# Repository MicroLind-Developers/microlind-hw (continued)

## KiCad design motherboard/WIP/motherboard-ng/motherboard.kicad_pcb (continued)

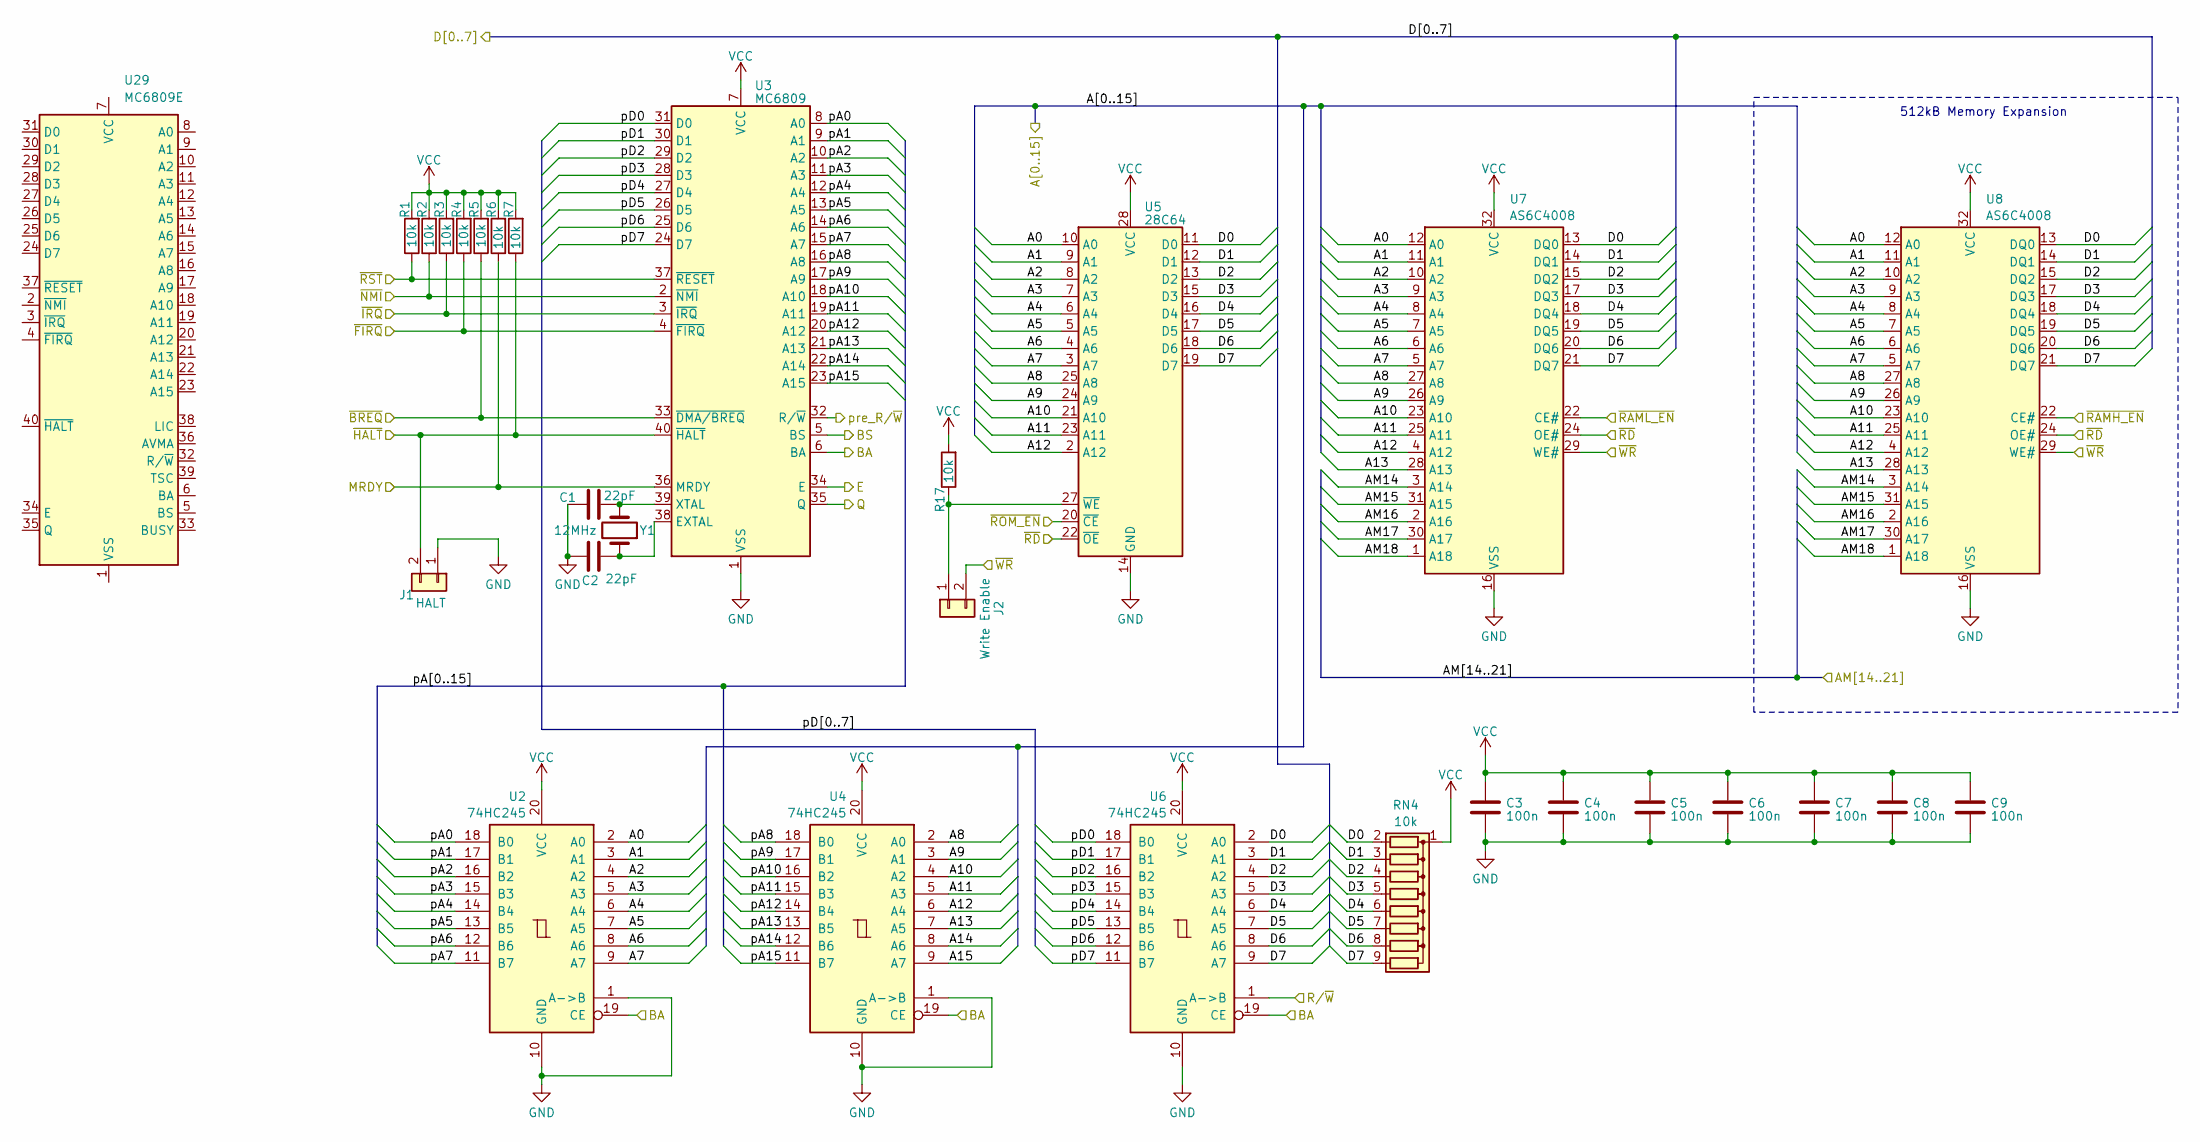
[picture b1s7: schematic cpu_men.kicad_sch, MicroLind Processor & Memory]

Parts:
C1, C2: 22pF; C_Disc_D5.0mm_W2.5mm_P2.50mm
C3, C4, C5, C6, C7, C8, C9: 100n; C_Disc_D5.0mm_W2.5mm_P2.50mm
J1: HALT; PinHeader_1x02_P2.54mm_Vertical
J2: Write Enable; PinHeader_1x02_P2.54mm_Vertical
R1, R2, R3, R4, R5, R6, R7, R17: 10k; R_Axial_DIN0204_L3.6mm_D1.6mm_P7.62mm_Horizontal
RN4: 10k; R_Array_SIP9
U2, U4, U6: 74HC245; DIP-20_W7.62mm_Socket
U3: MC6809; DIP-40_W15.24mm_Socket
U5: 28C64; DIP-28_W15.24mm_Socket
U7, U8: AS6C4008; DIP-32_W15.24mm_Socket
U29: MC6809E; DIP-40_W15.24mm
Y1: 12MHz; Crystal_HC49-U_Vertical

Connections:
/A0: U2.2 (A0), U5.10 (A0), U7.12 (A0), U8.12 (A0); also elsewhere on the board
/A1: U2.3 (A1), U5.9 (A1), U7.11 (A1), U8.11 (A1); also elsewhere on the board
/A2: U2.4 (A2), U5.8 (A2), U7.10 (A2), U8.10 (A2); also elsewhere on the board
/A3: U2.5 (A3), U5.7 (A3), U7.9 (A3), U8.9 (A3); also elsewhere on the board
/A4: U2.6 (A4), U5.6 (A4), U7.8 (A4), U8.8 (A4); also elsewhere on the board
/A5: U2.7 (A5), U5.5 (A5), U7.7 (A5), U8.7 (A5); also elsewhere on the board
/A6: U2.8 (A6), U5.4 (A6), U7.6 (A6), U8.6 (A6); also elsewhere on the board
/A7: U2.9 (A7), U5.3 (A7), U7.5 (A7), U8.5 (A7); also elsewhere on the board
/A8: U4.2 (A0), U5.25 (A8), U7.27 (A8), U8.27 (A8); also elsewhere on the board
/A9: U4.3 (A1), U5.24 (A9), U7.26 (A9), U8.26 (A9); also elsewhere on the board
/A10: U4.4 (A2), U5.21 (A10), U7.23 (A10), U8.23 (A10); also elsewhere on the board
/A11: U4.5 (A3), U5.23 (A11), U7.25 (A11), U8.25 (A11); also elsewhere on the board
/A12: U4.6 (A4), U5.2 (A12), U7.4 (A12), U8.4 (A12); also elsewhere on the board
/A13: U4.7 (A5), U7.28 (A13), U8.28 (A13); also elsewhere on the board
/A14: U4.8 (A6); also elsewhere on the board
/A15: U4.9 (A7); also elsewhere on the board
/AM14: U7.3 (A14), U8.3 (A14); also elsewhere on the board
/AM15: U7.31 (A15), U8.31 (A15); also elsewhere on the board
/AM16: U7.2 (A16), U8.2 (A16); also elsewhere on the board
/AM17: U7.30 (A17), U8.30 (A17); also elsewhere on the board
/AM18: U7.1 (A18), U8.1 (A18); also elsewhere on the board
/Address-Logic/BA: U2.19 (CE), U3.6 (BA), U4.19 (CE), U6.19 (CE); also elsewhere on the board
/Address-Logic/BS: U3.5 (BS); also elsewhere on the board
/Address-Logic/Q: U3.35 (Q); also elsewhere on the board
/Address-Logic/pre_R/~W: U3.32 (R/~W); also elsewhere on the board
/Address-Logic/~RAMH_EN: U8.22 (CE#); also elsewhere on the board
/Address-Logic/~RAML_EN: U7.22 (CE#); also elsewhere on the board
/Address-Logic/~ROM_EN: U5.20 (~CE); also elsewhere on the board
/CPU_MEM/MRDY: R6.1, U3.36 (MRDY)
/CPU_MEM/pA0: U2.18 (B0), U3.8 (A0)
/CPU_MEM/pA1: U2.17 (B1), U3.9 (A1)
/CPU_MEM/pA2: U2.16 (B2), U3.10 (A2)
/CPU_MEM/pA3: U2.15 (B3), U3.11 (A3)
/CPU_MEM/pA4: U2.14 (B4), U3.12 (A4)
/CPU_MEM/pA5: U2.13 (B5), U3.13 (A5)
/CPU_MEM/pA6: U2.12 (B6), U3.14 (A6)
/CPU_MEM/pA7: U2.11 (B7), U3.15 (A7)
/CPU_MEM/pA8: U3.16 (A8), U4.18 (B0)
/CPU_MEM/pA9: U3.17 (A9), U4.17 (B1)
/CPU_MEM/pA10: U3.18 (A10), U4.16 (B2)
/CPU_MEM/pA11: U3.19 (A11), U4.15 (B3)
/CPU_MEM/pA12: U3.20 (A12), U4.14 (B4)
/CPU_MEM/pA13: U3.21 (A13), U4.13 (B5)
/CPU_MEM/pA14: U3.22 (A14), U4.12 (B6)
/CPU_MEM/pA15: U3.23 (A15), U4.11 (B7)
/CPU_MEM/pD0: U3.31 (D0), U6.18 (B0)
/CPU_MEM/pD1: U3.30 (D1), U6.17 (B1)
/CPU_MEM/pD2: U3.29 (D2), U6.16 (B2)
/CPU_MEM/pD3: U3.28 (D3), U6.15 (B3)
/CPU_MEM/pD4: U3.27 (D4), U6.14 (B4)
/CPU_MEM/pD5: U3.26 (D5), U6.13 (B5)
/CPU_MEM/pD6: U3.25 (D6), U6.12 (B6)
/CPU_MEM/pD7: U3.24 (D7), U6.11 (B7)
/CPU_MEM/~FIRQ: R4.1, U3.4 (~FIRQ); also elsewhere on the board
/CPU_MEM/~HALT: J1.2, R7.1, U3.40 (~HALT)
/CPU_MEM/~IRQ: R3.1, U3.3 (~IRQ); also elsewhere on the board
/CPU_MEM/~NMI: R2.1, U3.2 (~NMI)
/D0: RN4.2 (R1), U5.11 (D0), U6.2 (A0), U7.13 (DQ0), U8.13 (DQ0); also elsewhere on the board
/D1: RN4.3 (R2), U5.12 (D1), U6.3 (A1), U7.14 (DQ1), U8.14 (DQ1); also elsewhere on the board
/D2: RN4.4 (R3), U5.13 (D2), U6.4 (A2), U7.15 (DQ2), U8.15 (DQ2); also elsewhere on the board
/D3: RN4.5 (R4), U5.15 (D3), U6.5 (A3), U7.17 (DQ3), U8.17 (DQ3); also elsewhere on the board
/D4: RN4.6 (R5), U5.16 (D4), U6.6 (A4), U7.18 (DQ4), U8.18 (DQ4); also elsewhere on the board
/D5: RN4.7 (R6), U5.17 (D5), U6.7 (A5), U7.19 (DQ5), U8.19 (DQ5); also elsewhere on the board
/D6: RN4.8 (R7), U5.18 (D6), U6.8 (A6), U7.20 (DQ6), U8.20 (DQ6); also elsewhere on the board
/D7: RN4.9 (R8), U5.19 (D7), U6.9 (A7), U7.21 (DQ7), U8.21 (DQ7); also elsewhere on the board
/Expansion Ports/E: U3.34 (E); also elsewhere on the board
/Expansion Ports/R/~W: U6.1 (A->B); also elsewhere on the board
/Expansion Ports/~BREQ: R5.1, U3.33 (~DMA/BREQ); also elsewhere on the board
/Expansion Ports/~RD: U5.22 (~OE), U7.24 (OE#), U8.24 (OE#); also elsewhere on the board
/Expansion Ports/~RST: R1.1, U3.37 (~RESET); also elsewhere on the board
/Expansion Ports/~WR: J2.2, U7.29 (WE#), U8.29 (WE#); also elsewhere on the board
unnamed: J2.1, R17.1, U5.27 (~WE)
unnamed: C2.1, U3.38 (EXTAL), Y1.1
unnamed: C1.1, U3.39 (XTAL), Y1.2

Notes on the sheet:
512kB Memory Expansion

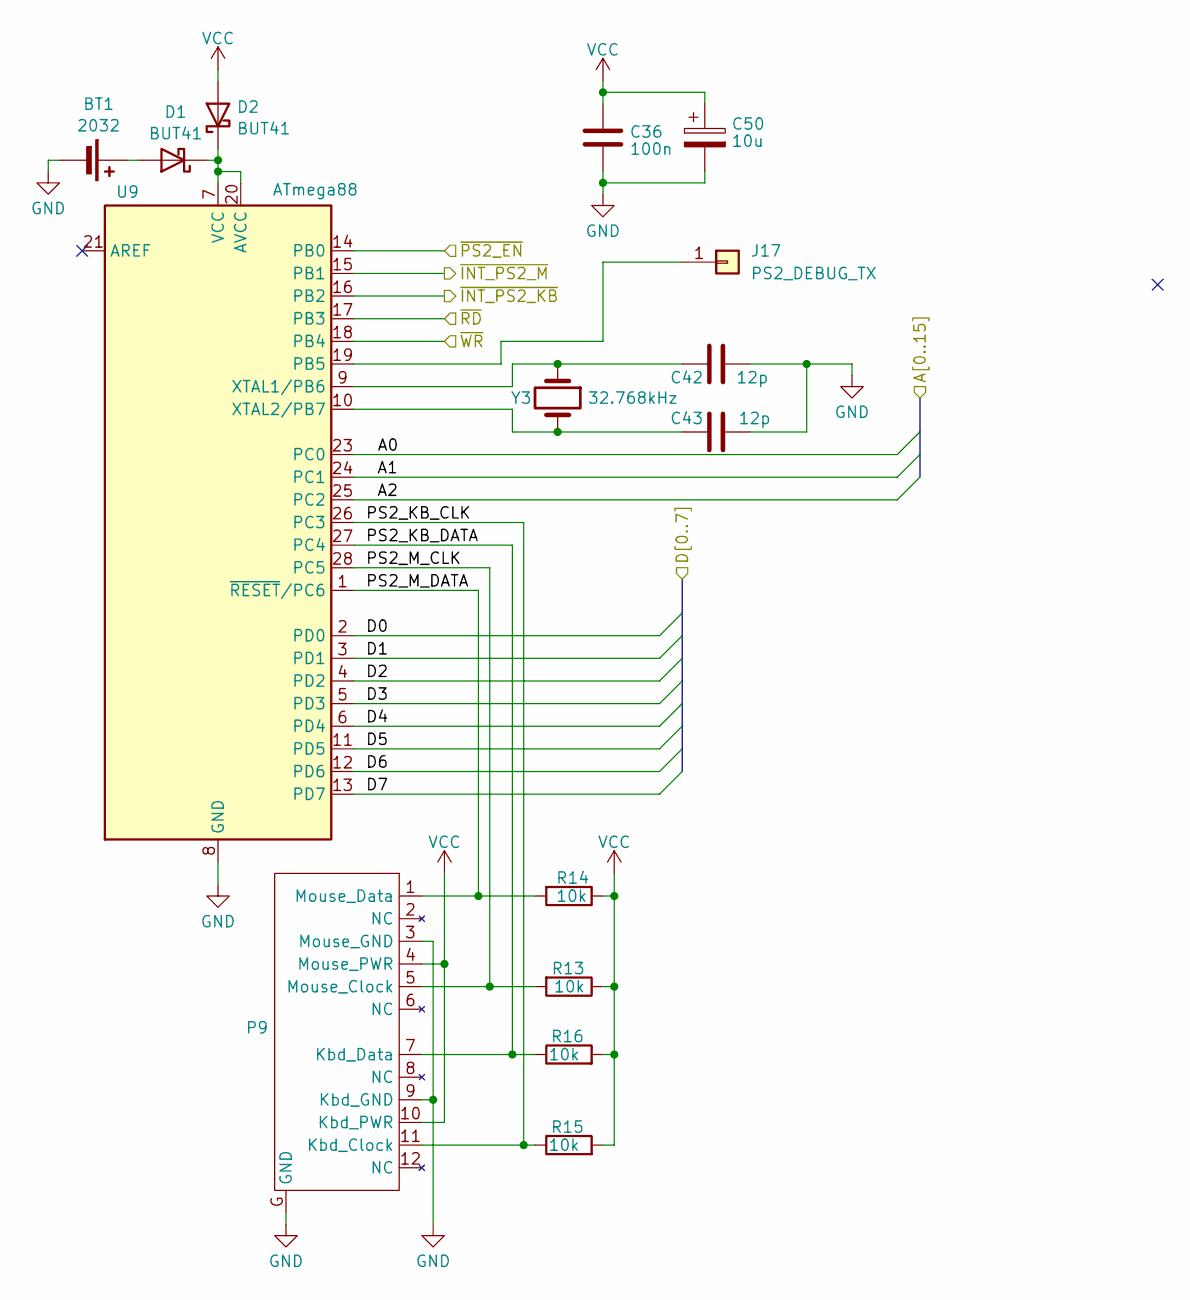
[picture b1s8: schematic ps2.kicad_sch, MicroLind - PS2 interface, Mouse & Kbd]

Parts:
BT1: 2032; HU2032-CoinCellHolder
C36: 100n; C_Disc_D5.0mm_W2.5mm_P2.50mm
C42, C43: 12p; C_Disc_D5.0mm_W2.5mm_P2.50mm
C50: 10u; CP_Radial_D4.0mm_P2.00mm
D1, D2: BUT41; D_A-405_P7.62mm_Horizontal
J17: PS2_DEBUG_TX; PinHeader_1x01_P2.54mm_Vertical
P9: 2xPS2-Mini-Din
R13, R14, R15, R16: 10k; R_Axial_DIN0204_L3.6mm_D1.6mm_P7.62mm_Horizontal
U9: ATmega88; DIP-28_W7.62mm_Socket
Y3: 32.768kHz; Crystal_DS10_D1.0mm_L4.3mm_Vertical

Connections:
/A0: U9.23 (PC0); also elsewhere on the board
/A1: U9.24 (PC1); also elsewhere on the board
/A2: U9.25 (PC2); also elsewhere on the board
/Address-Logic/~PS2_EN: U9.14 (PB0); also elsewhere on the board
/D0: U9.2 (PD0); also elsewhere on the board
/D1: U9.3 (PD1); also elsewhere on the board
/D2: U9.4 (PD2); also elsewhere on the board
/D3: U9.5 (PD3); also elsewhere on the board
/D4: U9.6 (PD4); also elsewhere on the board
/D5: U9.11 (PD5); also elsewhere on the board
/D6: U9.12 (PD6); also elsewhere on the board
/D7: U9.13 (PD7); also elsewhere on the board
/Expansion Ports/~RD: U9.17 (PB3); also elsewhere on the board
/Expansion Ports/~WR: U9.18 (PB4); also elsewhere on the board
/PS2/PS2_KB_CLK: P9.11 (Kbd_Clock), R15.1, U9.26 (PC3)
/PS2/PS2_KB_DATA: P9.7 (Kbd_Data), R16.1, U9.27 (PC4)
/PS2/PS2_M_CLK: P9.5 (Mouse_Clock), R13.2, U9.28 (PC5)
/PS2/PS2_M_DATA: P9.1 (Mouse_Data), R14.2, U9.1 (~RESET/PC6)
/~IRQ_8: U9.16 (PB2); also elsewhere on the board
/~IRQ_12: U9.15 (PB1); also elsewhere on the board
unnamed: BT1.1 (+), D1.2 (A)
unnamed: D1.1 (K), D2.1 (K), U9.7 (VCC), U9.20 (AVCC)
unnamed: J17.1, U9.19 (PB5)
unnamed: C42.1, U9.9 (XTAL1/PB6), Y3.1
unnamed: C43.1, U9.10 (XTAL2/PB7), Y3.2

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
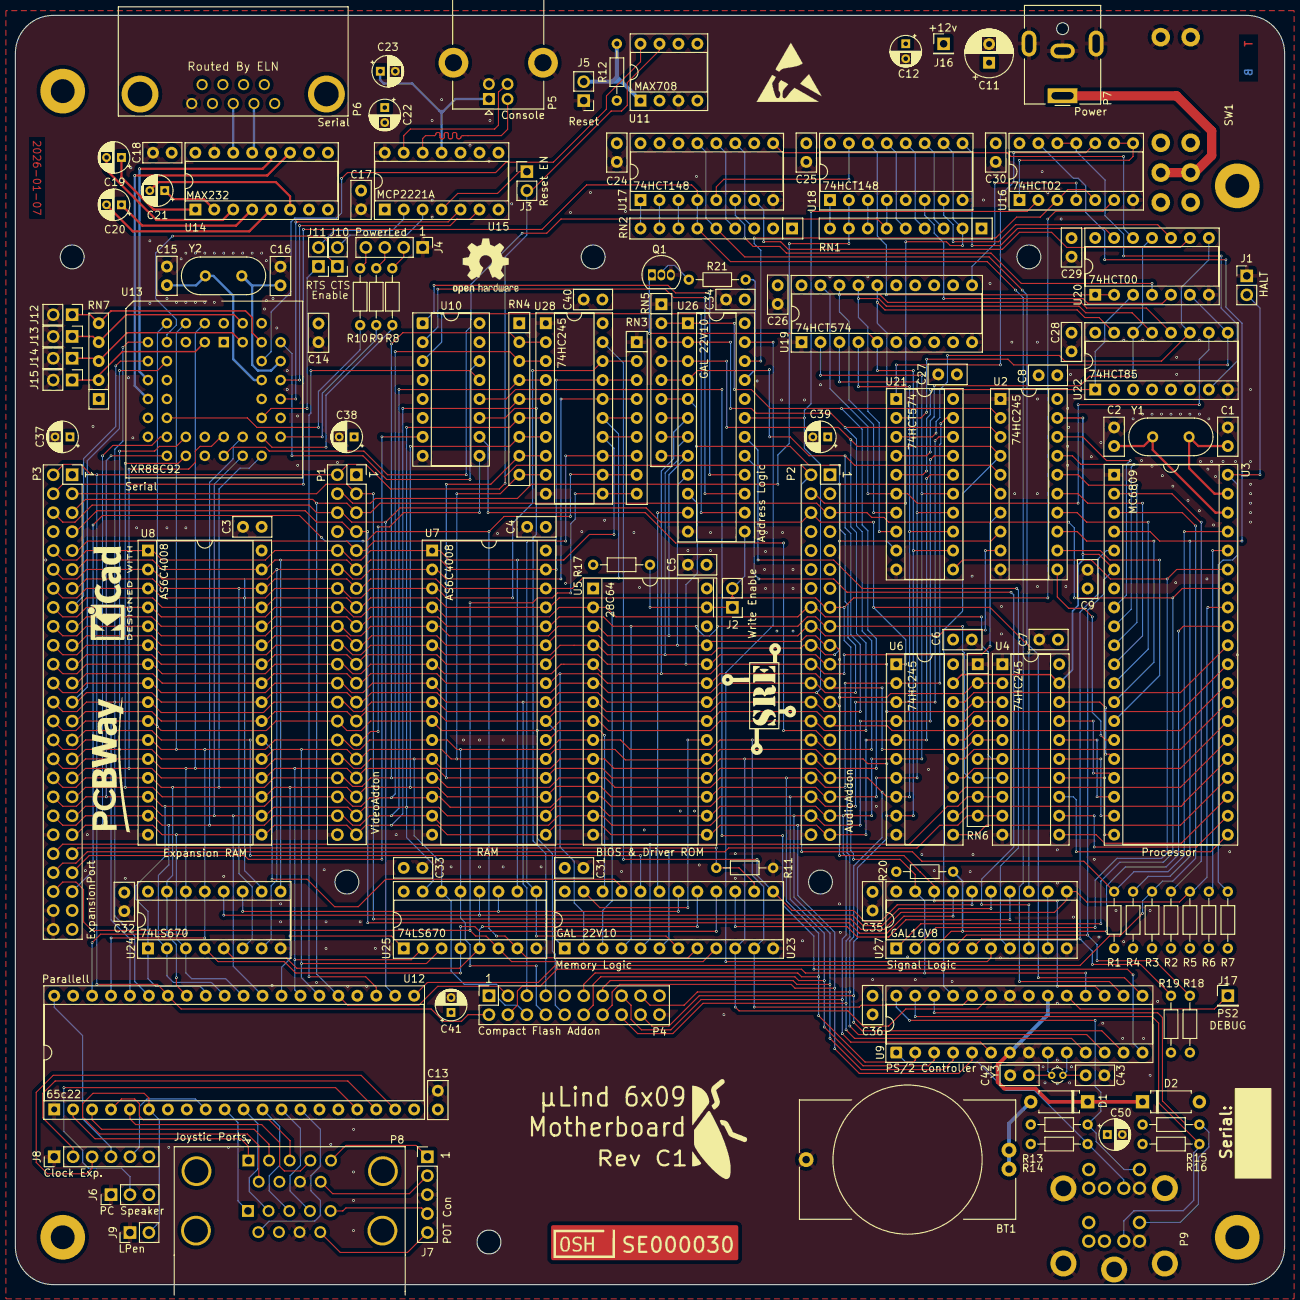
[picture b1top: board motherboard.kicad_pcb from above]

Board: 4 copper layers, 170.2 x 170.2 mm, 140 parts (0 on the bottom side), 205 nets.

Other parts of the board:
G1: LOGO; sre

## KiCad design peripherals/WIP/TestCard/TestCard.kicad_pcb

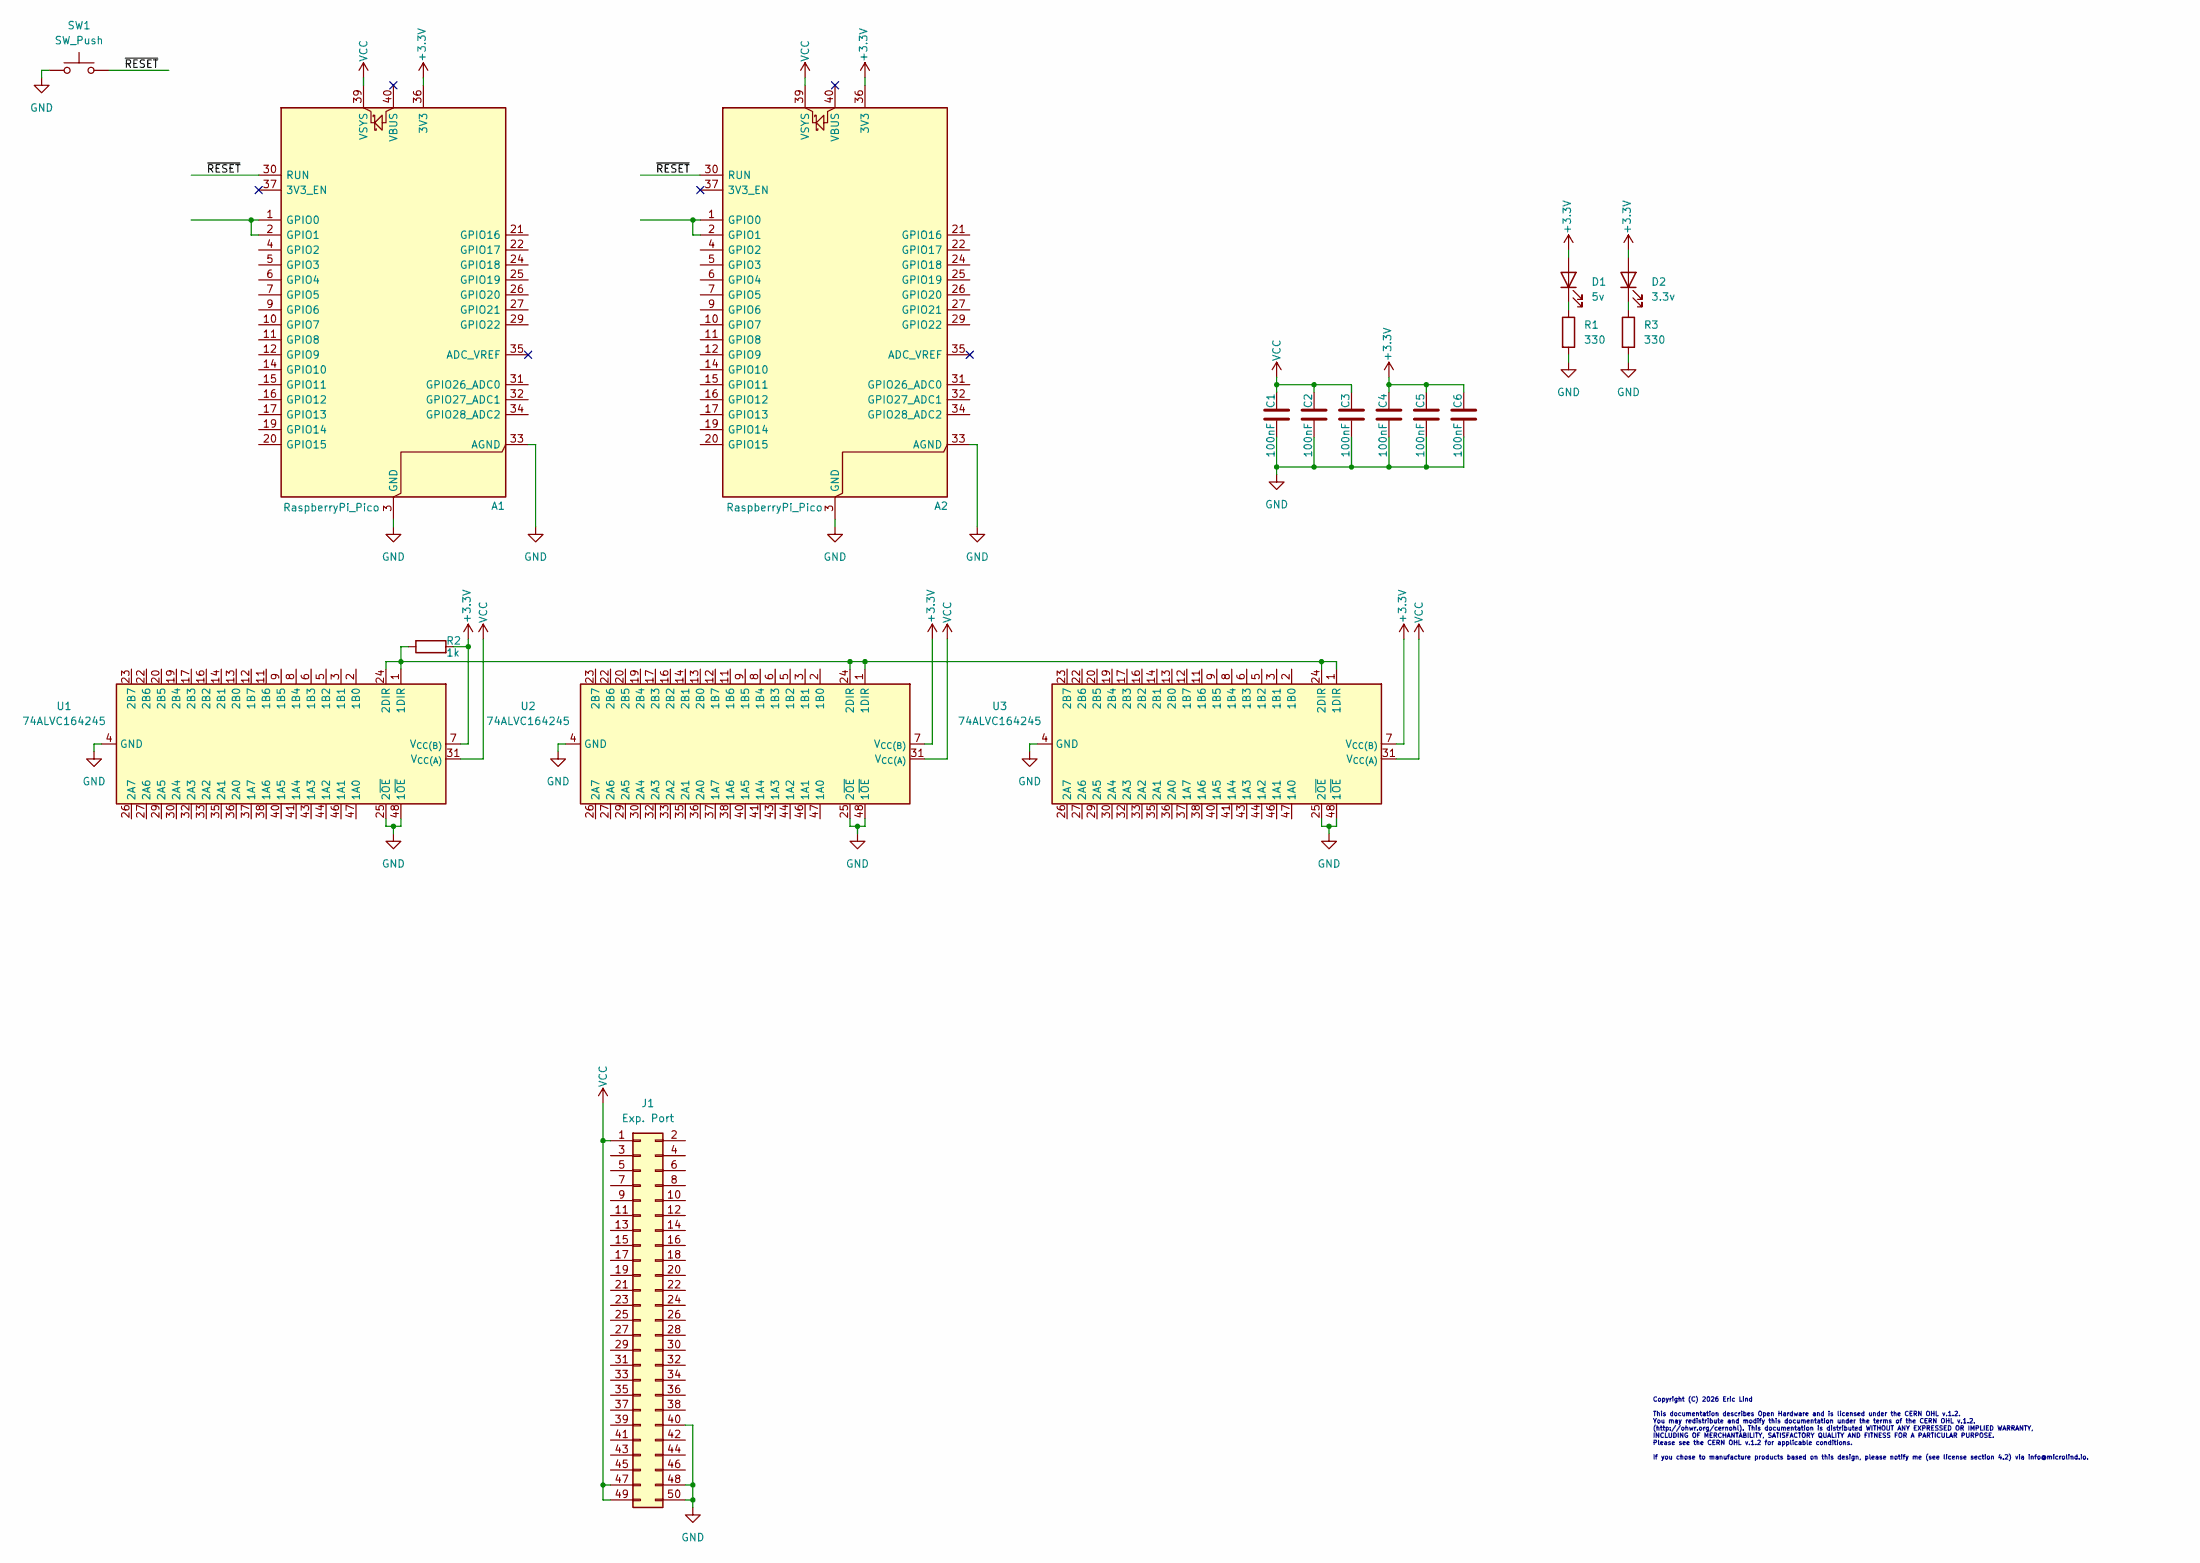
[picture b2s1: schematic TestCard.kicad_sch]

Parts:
A1, A2: RaspberryPi_Pico; RaspberryPi_Pico_Common_Unspecified
C1, C2, C3, C4, C5, C6: 100nF; C_0805_2012Metric
D1: 5v; LED_0805_2012Metric
D2: 3.3v; LED_0805_2012Metric
J1: Exp. Port; PinHeader_2x25_P2.54mm_Horizontal
R1, R3: 330; R_0805_2012Metric
R2: 1k; R_0805_2012Metric
SW1: SW_Push; SW_Push_SPST_NO_Alps_SKRK
U1, U2, U3: 74ALVC164245; TSSOP-48_6.1x12.5mm_P0.5mm

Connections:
+3.3V: A1.36 (3V3), A2.36 (3V3), C4.1, C5.1, C6.1, D1.2 (A), D2.2 (A), R2.2, U1.7 (V_{CC(B)}), U1.18 (V_{CC(B)}), U2.7 (V_{CC(B)}), U2.18 (V_{CC(B)}), U3.7 (V_{CC(B)}), U3.18 (V_{CC(B)})
/~RESET: A1.30 (RUN), A2.30 (RUN), SW1.2
GND: A1.3 (GND), A1.8 (GND), A1.13 (GND), A1.18 (GND), A1.23 (GND), A1.28 (GND), A1.33 (AGND), A1.38 (GND), A2.3 (GND), A2.8 (GND), A2.13 (GND), A2.18 (GND), A2.23 (GND), A2.28 (GND), A2.33 (AGND), A2.38 (GND), C1.2, C2.2, C3.2, C4.2, C5.2, C6.2, J1.40, J1.48, J1.50, R1.2, R3.2, SW1.1, U1.4 (GND), U1.10 (GND), U1.15 (GND), U1.21 (GND), U1.25 (2~OE), U1.28 (GND), U1.34 (GND), U1.39 (GND), U1.45 (GND), U1.48 (1~OE), U2.4 (GND), U2.10 (GND), U2.15 (GND), U2.21 (GND), U2.25 (2~OE), U2.28 (GND), U2.34 (GND), U2.39 (GND), U2.45 (GND), U2.48 (1~OE), U3.4 (GND), U3.10 (GND), U3.15 (GND), U3.21 (GND), U3.25 (2~OE), U3.28 (GND), U3.34 (GND), U3.39 (GND), U3.45 (GND), U3.48 (1~OE)
unnamed: A1.1 (GPIO0), A1.2 (GPIO1)
unnamed: A2.1 (GPIO0), A2.2 (GPIO1)
unnamed: D1.1 (K), R1.1
unnamed: D2.1 (K), R3.1
unnamed: R2.1, U1.1 (1DIR), U1.24 (2DIR), U2.1 (1DIR), U2.24 (2DIR), U3.1 (1DIR), U3.24 (2DIR)
VCC: A1.39 (VSYS), A2.39 (VSYS), C1.1, C2.1, C3.1, J1.1, J1.47, J1.49, U1.31 (V_{CC(A)}), U1.42 (V_{CC(A)}), U2.31 (V_{CC(A)}), U2.42 (V_{CC(A)}), U3.31 (V_{CC(A)}), U3.42 (V_{CC(A)})

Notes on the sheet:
Copyright (C) 2026 Eric Lind This documentation describes Open Hardware and is licensed under the CERN OHL v.1.2. You may redistribute and modify this documentation under the terms of the CERN OHL v.1.2. (http://ohwr.org/cernohl). This documentation is distributed WITHOUT ANY EXPRESSED OR IMPLIED W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

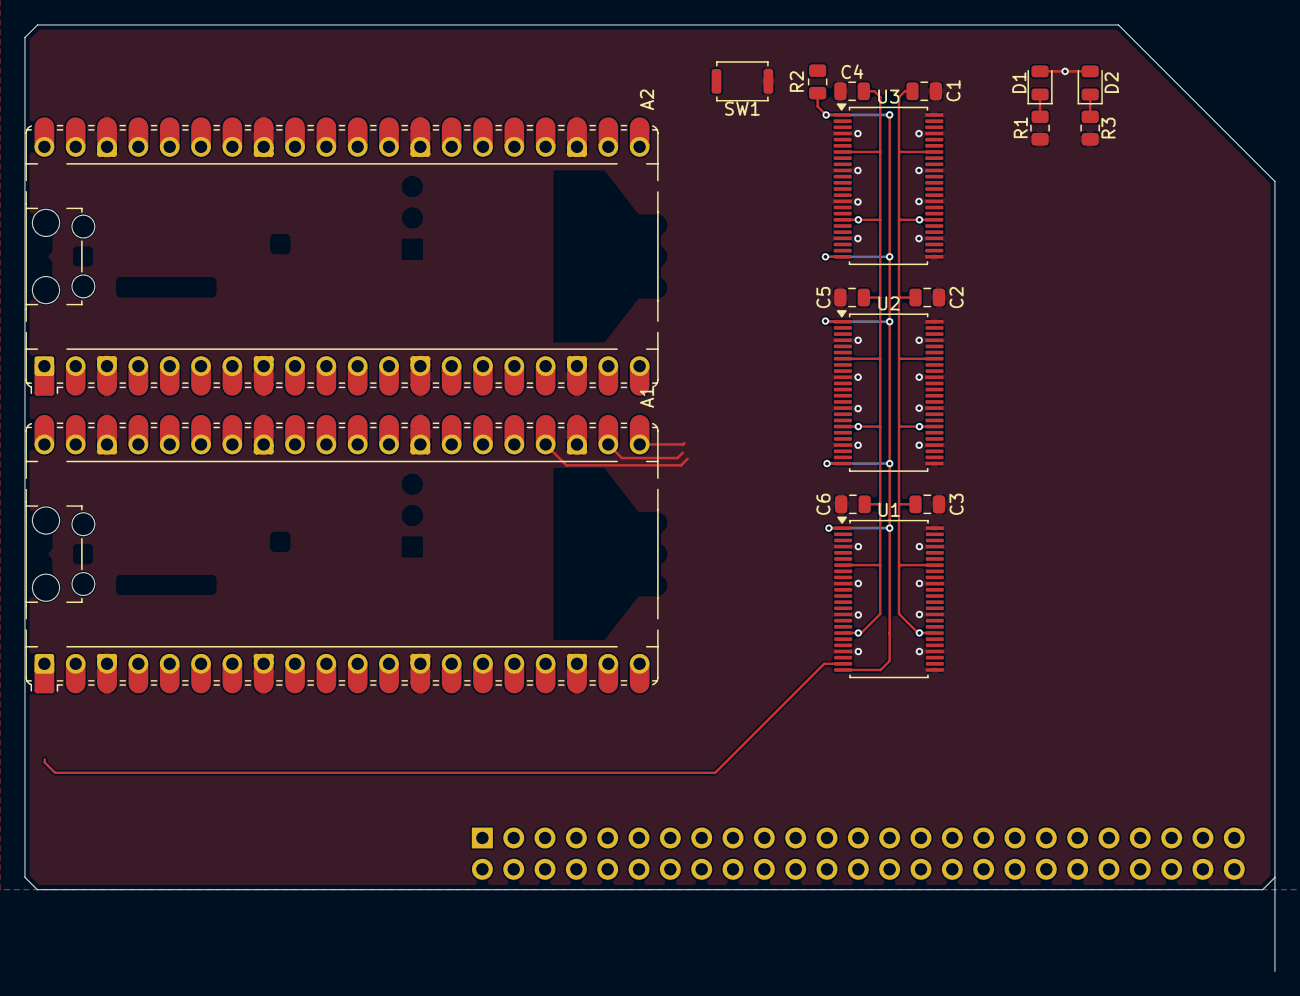
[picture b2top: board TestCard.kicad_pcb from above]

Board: 4 copper layers, 101.3 x 76.7 mm, 18 parts (1 on the bottom side), 9 nets.

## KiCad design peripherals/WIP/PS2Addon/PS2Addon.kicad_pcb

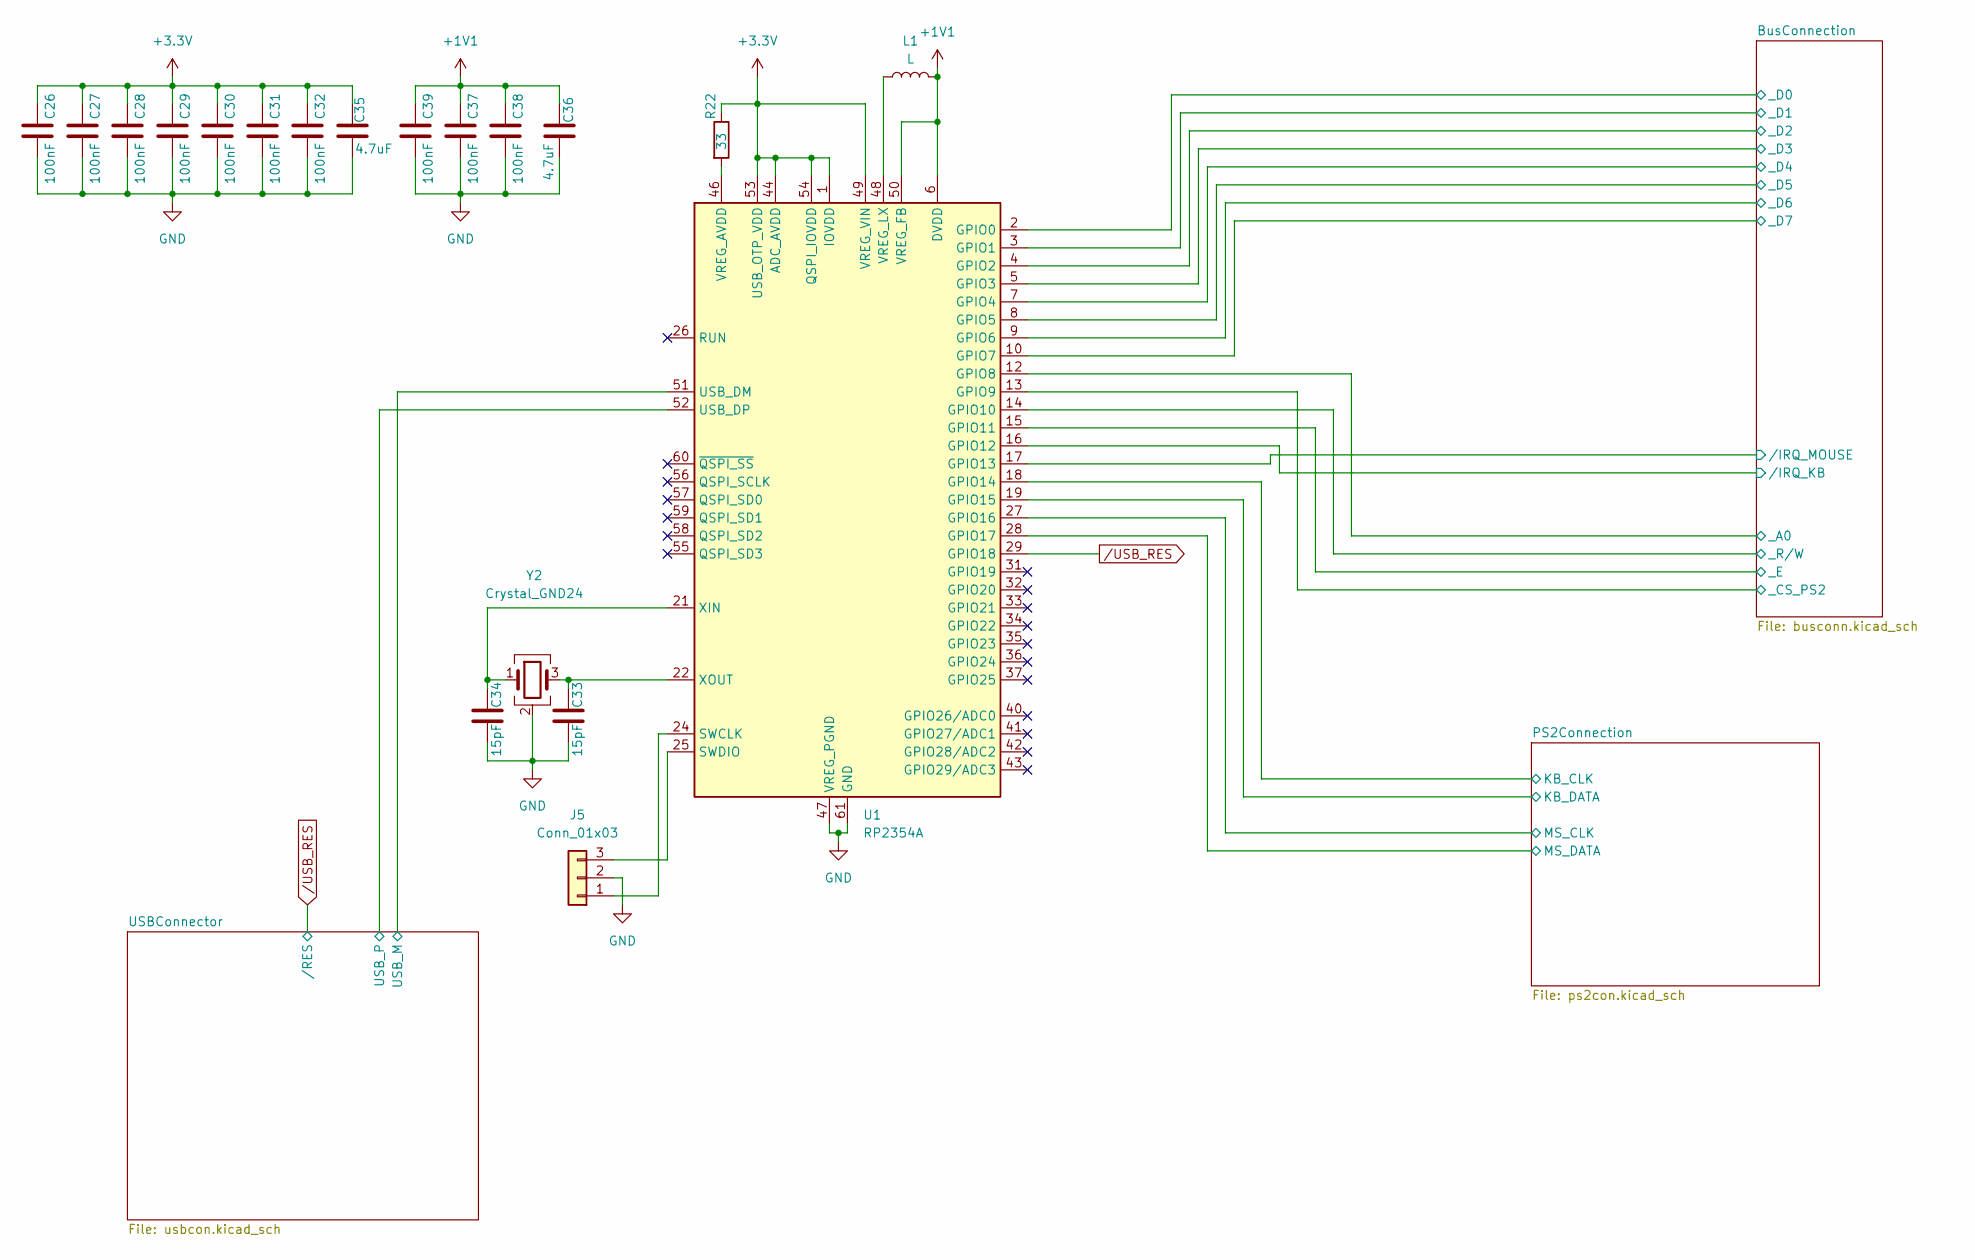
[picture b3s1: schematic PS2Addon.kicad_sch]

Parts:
C26, C27, C28, C29, C30, C31, C32, C37, C38, C39: 100nF; C_0402_1005Metric
C33, C34: 15pF; C_0402_1005Metric
C35, C36: 4.7uF; C_0402_1005Metric
J5: Conn_01x03; JST_SH_SM03B-SRSS-TB_1x03-1MP_P1.00mm_Horizontal
L1: L; Untitled
R22: 33; R_0402_1005Metric
U1: RP2354A; QFN-60-1EP_7x7mm_P0.4mm_EP3.4x3.4mm
Y2: Crystal_GND24; Crystal_SMD_3225-4Pin_3.2x2.5mm

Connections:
+1V1: C36.1, C37.1, C38.1, C39.1, L1.2, U1.6 (DVDD), U1.23 (DVDD), U1.39 (DVDD), U1.50 (VREG_FB)
+3.3V: C26.1, C27.1, C28.1, C29.1, C30.1, C31.1, C32.1, C35.1, R22.1, U1.1 (IOVDD), U1.11 (IOVDD), U1.20 (IOVDD), U1.30 (IOVDD), U1.38 (IOVDD), U1.44 (ADC_AVDD), U1.45 (IOVDD), U1.49 (VREG_VIN), U1.53 (USB_OTP_VDD), U1.54 (QSPI_IOVDD); also elsewhere on the board
/BusConnection/_A0: U1.12 (GPIO8); also elsewhere on the board
/BusConnection/_CS_PS2: U1.13 (GPIO9); also elsewhere on the board
/BusConnection/_D0: U1.2 (GPIO0); also elsewhere on the board
/BusConnection/_D1: U1.3 (GPIO1); also elsewhere on the board
/BusConnection/_D2: U1.4 (GPIO2); also elsewhere on the board
/BusConnection/_D3: U1.5 (GPIO3); also elsewhere on the board
/BusConnection/_D4: U1.7 (GPIO4); also elsewhere on the board
/BusConnection/_D5: U1.8 (GPIO5); also elsewhere on the board
/BusConnection/_D6: U1.9 (GPIO6); also elsewhere on the board
/BusConnection/_D7: U1.10 (GPIO7); also elsewhere on the board
/BusConnection/_E: U1.15 (GPIO11); also elsewhere on the board
/BusConnection/_R/W: U1.14 (GPIO10); also elsewhere on the board
/BusConnection//IRQ_KB: U1.16 (GPIO12); also elsewhere on the board
/BusConnection//IRQ_MOUSE: U1.17 (GPIO13); also elsewhere on the board
/PS2Connection/KB_CLK: U1.18 (GPIO14); also elsewhere on the board
/PS2Connection/KB_DATA: U1.19 (GPIO15); also elsewhere on the board
/PS2Connection/MS_CLK: U1.27 (GPIO16); also elsewhere on the board
/PS2Connection/MS_DATA: U1.28 (GPIO17); also elsewhere on the board
/USBConnector/USB_M: U1.51 (USB_DM); also elsewhere on the board
/USBConnector/USB_P: U1.52 (USB_DP); also elsewhere on the board
GND: C26.2, C27.2, C28.2, C29.2, C30.2, C31.2, C32.2, C33.2, C34.2, C35.2, C36.2, C37.2, C38.2, C39.2, J5.2, U1.47 (VREG_PGND), U1.61 (GND), Y2.2 (G), Y2.4 (G); also elsewhere on the board
unnamed: J5.1, U1.24 (SWCLK)
unnamed: J5.3, U1.25 (SWDIO)
unnamed: R22.2, U1.46 (VREG_AVDD)
unnamed: L1.1, U1.48 (VREG_LX)
unnamed: C34.1, U1.21 (XIN), Y2.1
unnamed: C33.1, U1.22 (XOUT), Y2.3
/USB_RES: U1.29 (GPIO18); also elsewhere on the board

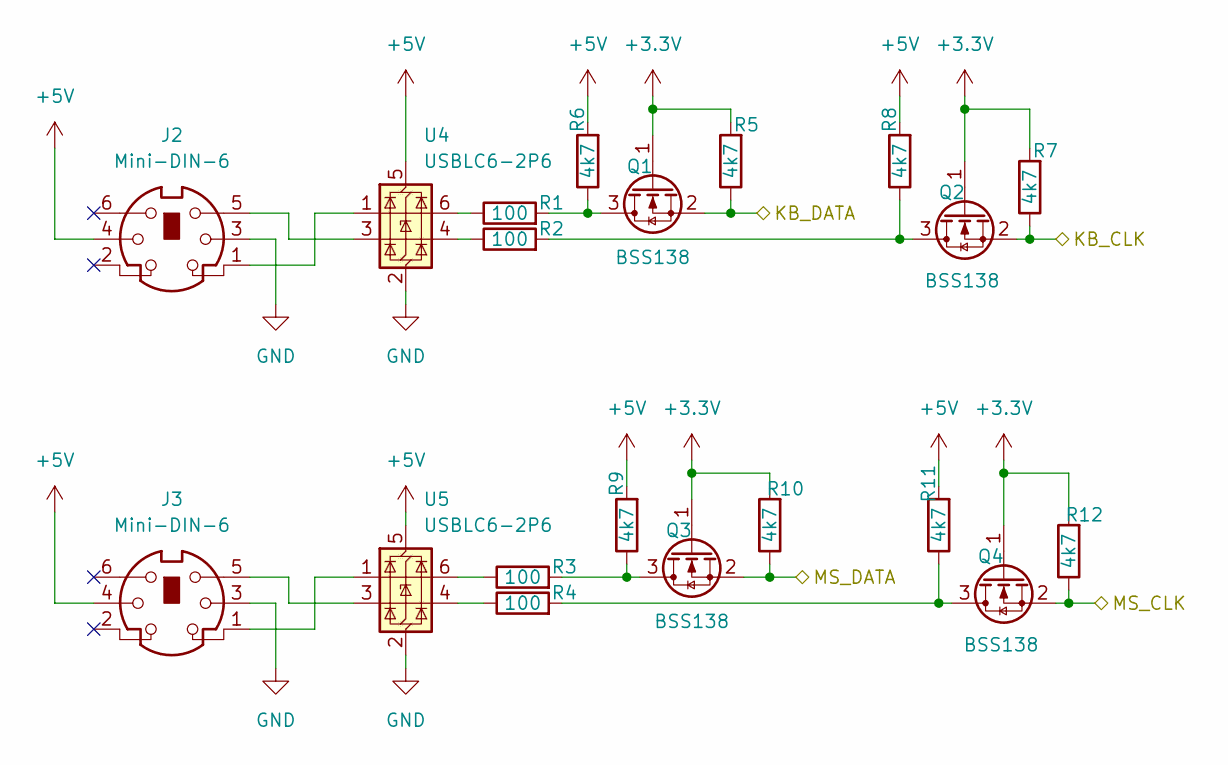
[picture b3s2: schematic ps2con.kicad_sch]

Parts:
J2, J3: Mini-DIN-6
Q1, Q2, Q3, Q4: BSS138; SOT-23
R1, R2, R3, R4: 100; R_0402_1005Metric
R5, R6, R7, R8, R9, R10, R11, R12: 4k7; R_0402_1005Metric
U4, U5: USBLC6-2P6; SOT-666

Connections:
+3.3V: Q1.1 (G), Q2.1 (G), Q3.1 (G), Q4.1 (G), R5.2, R7.2, R10.2, R12.2; also elsewhere on the board
+5V: J2.4, J3.4, R6.2, R8.2, R9.2, R11.2, U4.5 (VBUS), U5.5 (VBUS); also elsewhere on the board
/PS2Connection/KB_CLK: Q2.2 (S), R7.1; also elsewhere on the board
/PS2Connection/KB_DATA: Q1.2 (S), R5.1; also elsewhere on the board
/PS2Connection/MS_CLK: Q4.2 (S), R12.1; also elsewhere on the board
/PS2Connection/MS_DATA: Q3.2 (S), R10.1; also elsewhere on the board
GND: J2.3, J3.3, U4.2 (GND), U5.2 (GND); also elsewhere on the board
unnamed: J2.1, U4.1 (I/O1)
unnamed: J2.5, U4.3 (I/O2)
unnamed: J3.1, U5.1 (I/O1)
unnamed: J3.5, U5.3 (I/O2)
unnamed: Q1.3 (D), R1.2, R6.1
unnamed: Q2.3 (D), R2.2, R8.1
unnamed: Q3.3 (D), R3.2, R9.1
unnamed: Q4.3 (D), R4.2, R11.1
unnamed: R1.1, U4.6 (I/O1)
unnamed: R2.1, U4.4 (I/O2)
unnamed: R3.1, U5.6 (I/O1)
unnamed: R4.1, U5.4 (I/O2)
